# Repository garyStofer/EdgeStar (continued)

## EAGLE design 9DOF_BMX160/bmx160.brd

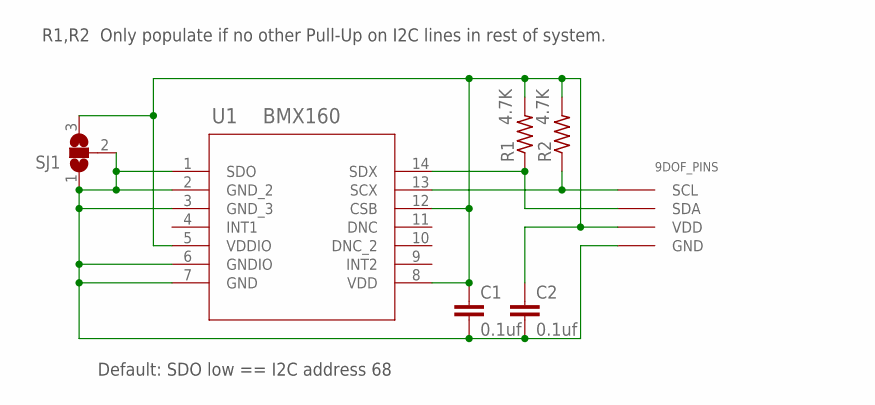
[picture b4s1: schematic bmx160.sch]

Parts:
C1, C2: 0.1uf; C0603K
MOD1: 9DOF_PINS
R1, R2: 4.7K; M0805
SJ1: SJ2W; SJ_2
U1: BMX160; BMX160_BOS-M

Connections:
GND: C1.2, C2.2, MOD1.GND, SJ1.1, SJ1.2, U1.1 (SDO), U1.2 (GND_2), U1.3 (GND_3), U1.6 (GNDIO), U1.7 (GND)
unnamed: MOD1.SDA, R1.1, U1.14 (SDX)
unnamed: MOD1.SCL, R2.1, U1.13 (SCX)
VDD: C1.1, C2.1, MOD1.VDD, R1.2, R2.2, SJ1.3, U1.5 (VDDIO), U1.8 (VDD), U1.12 (CSB)

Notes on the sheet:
Default: SDO low == I2C address 68
R1,R2 Only populate if no other Pull-Up on I2C lines in rest of system.

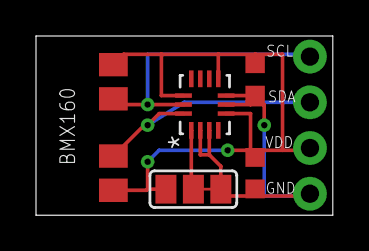
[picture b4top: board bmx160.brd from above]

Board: 2 copper layers, 16.5 x 10.0 mm, 7 parts (0 on the bottom side), 4 nets.

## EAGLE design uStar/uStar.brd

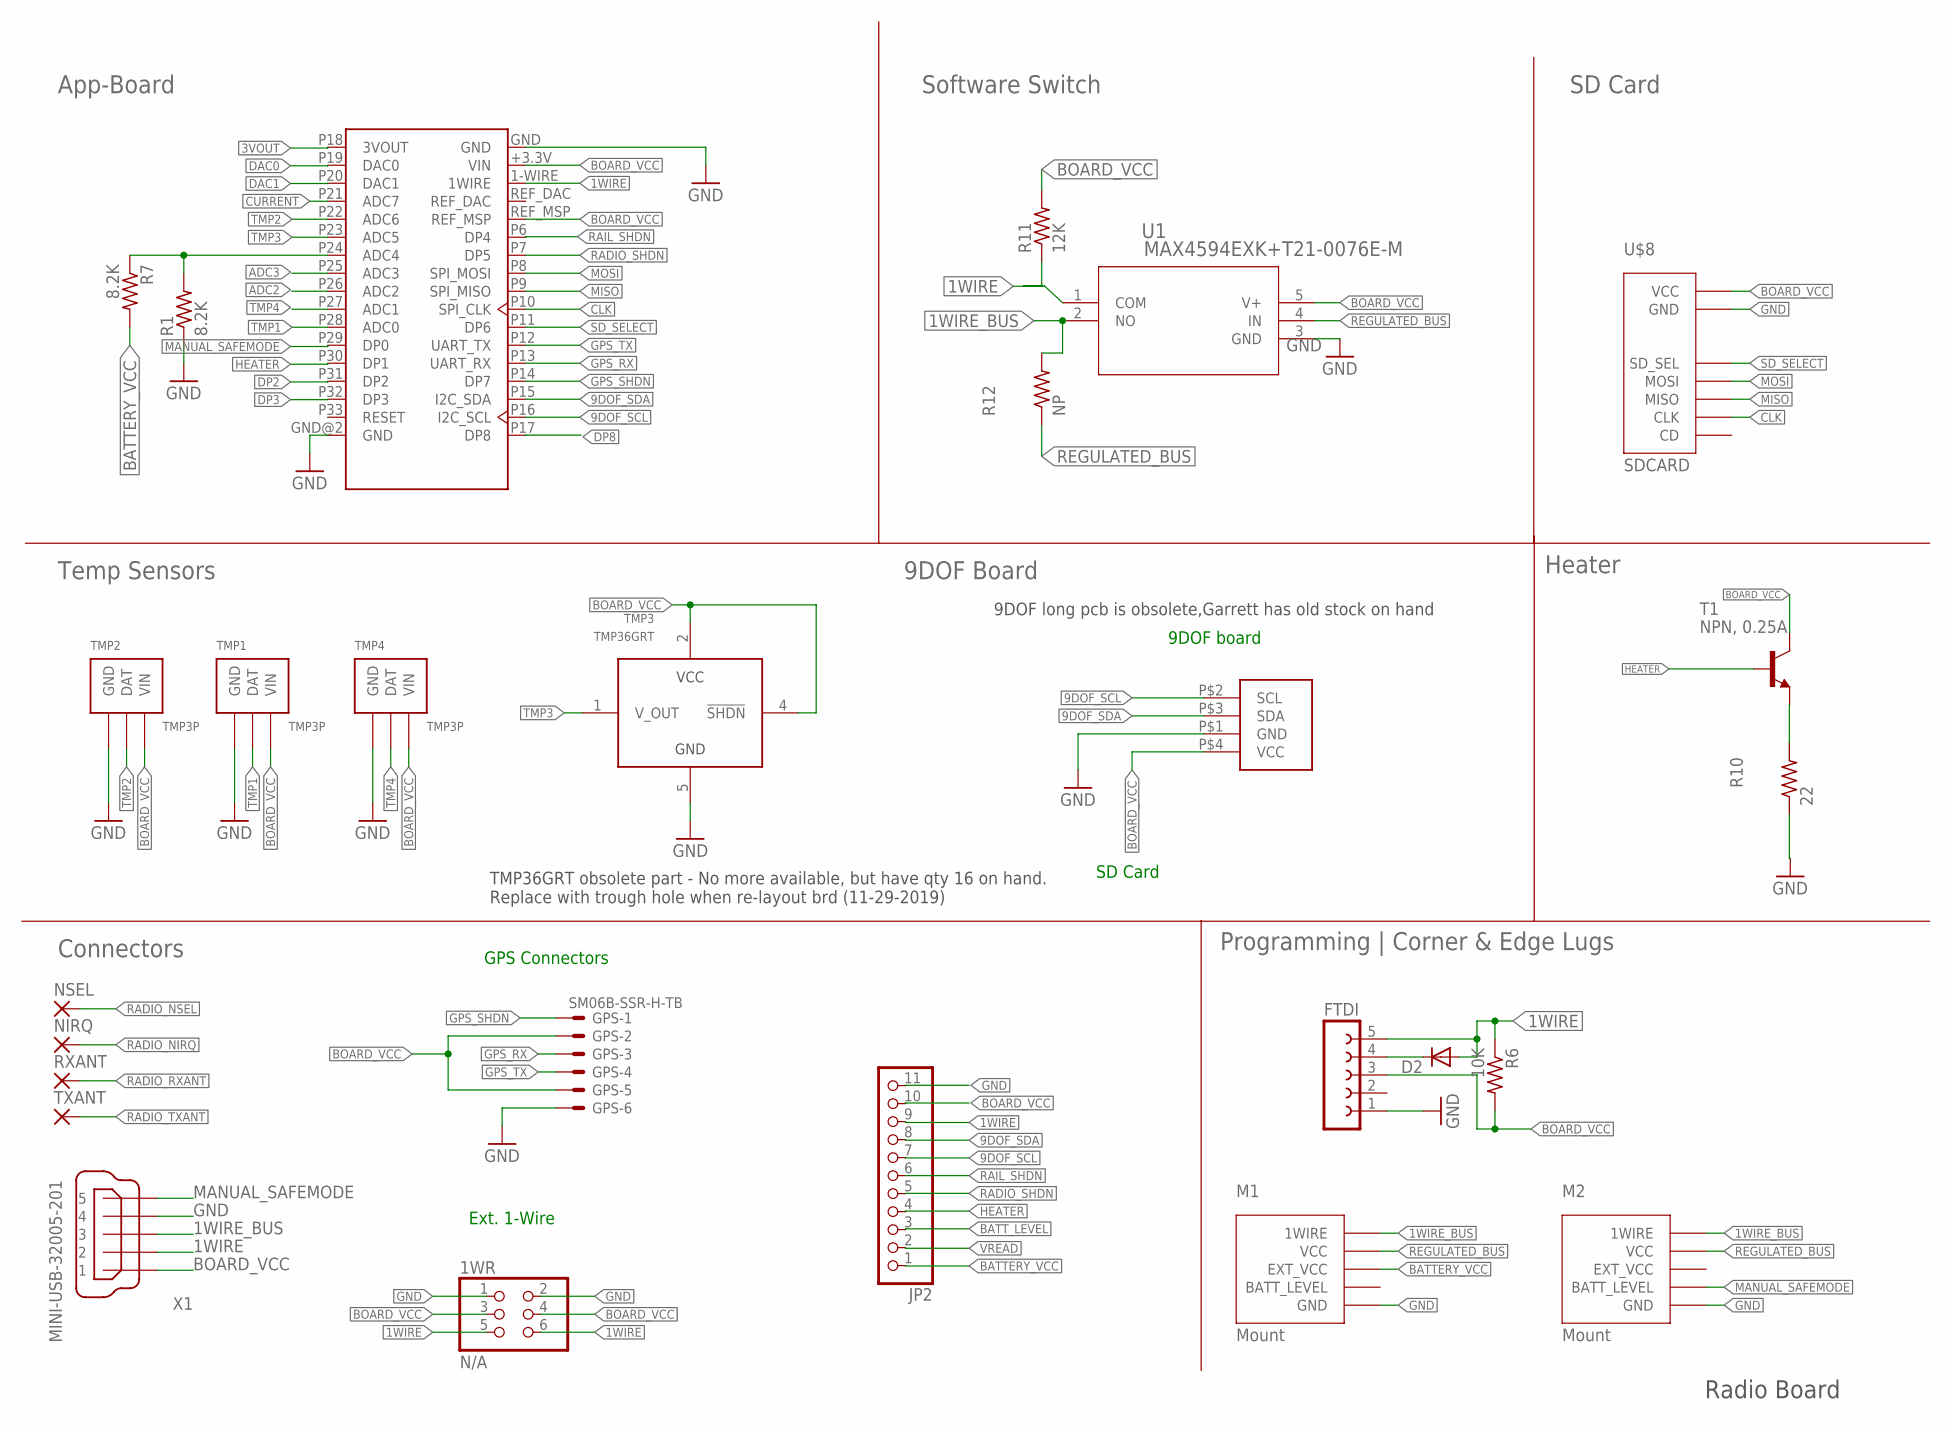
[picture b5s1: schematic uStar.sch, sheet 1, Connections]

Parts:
1WR: N/A; 2X03
D2: D-B260A; SMA-DO214AC
FTDI: FE05-1
GPS: SM06B-SSR-H-TB
JP2: PINHD-1X11; 1X11
M1, M2: Mount; 4X8MOUNT
NIRQ: 1,6/0,9
NSEL: 1,6/0,9
PCB1: 9DOF
R1, R7: 8.2K; R0805
R6: 10K; R0603
R10: 22; 0207/7
R11: 12K; R0805
R12: NP; R0805
RXANT: 1,6/0,9
T1: NPN, 0.25A; TO92-EBC-OVAL
TMP1, TMP2, TMP4: TMP3P
TMP3: TMP36GRT; SOT-23-5; DIGIKEY obsolete
TXANT: 1,6/0,9
U1: MAX4594EXK+T21-0076E-M; 21-0076E-M; DIGIKEY MAX4594EXK+TCT-ND
U$1: App-Board 1.2/1.3; APPCORE_RECEIVER
U$8: SDCARD; DIGIKEY 1568-1345-ND
X1: MINI-USB-32005-201; 32005-201

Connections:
1WIRE: 1WR.5, 1WR.6, D2.A, FTDI.5, JP2.9, R6.1, R11.1, U1.1 (COM), U$1.1-WIRE (1WIRE), X1.2
1WIRE_BUS: M1.P$2 (1WIRE), M1.P$5 (1WIRE), M2.P$2 (1WIRE), M2.P$5 (1WIRE), R12.2, U1.2 (NO), X1.3
3VOUT: U$1.P18 (3VOUT)
9DOF_SCL: JP2.7, PCB1.P$2 (SCL), U$1.P16 (I2C_SCL)
9DOF_SDA: JP2.8, PCB1.P$3 (SDA), U$1.P15 (I2C_SDA)
ADC2: U$1.P26 (ADC2)
ADC3: U$1.P25 (ADC3)
BATTERY_VCC: JP2.1, M1.P$3 (EXT_VCC), R7.2; also elsewhere on the board
BATT_LEVEL: JP2.3
BOARD_VCC: 1WR.3, 1WR.4, FTDI.3, GPS.2, GPS.5, JP2.10, PCB1.P$4 (VCC), R6.2, R11.2, T1.C, TMP1.P$3 (VIN), TMP2.P$3 (VIN), TMP3.2 (VCC), TMP3.4 (!SHDN), TMP4.P$3 (VIN), U1.5 (V+), U$1.+3.3V (VIN), U$1.REF_MSP, U$8.P$3 (VCC), X1.1; also elsewhere on the board
CLK: U$1.P10 (SPI_CLK), U$8.P$4 (CLK); also elsewhere on the board
CURRENT: U$1.P21 (ADC7); also elsewhere on the board
DAC0: U$1.P19 (DAC0)
DAC1: U$1.P20 (DAC1)
DP2: U$1.P31 (DP2)
DP3: U$1.P32 (DP3)
DP8: U$1.P17 (DP8)
GND: 1WR.1, 1WR.2, FTDI.1, GPS.6, JP2.11, M1.P$1 (GND), M1.P$8 (GND), M2.P$1 (GND), M2.P$8 (GND), PCB1.P$1 (GND), R1.1, R10.1, TMP1.P$1 (GND), TMP2.P$1 (GND), TMP3.5 (GND), TMP4.P$1 (GND), U1.3 (GND), U$1.GND, U$1.GND@2 (GND), U$8.P$5 (GND), X1.4; also elsewhere on the board
GPS_RX: GPS.3, U$1.P13 (UART_RX)
GPS_SHDN: GPS.1, U$1.P14 (DP7)
GPS_TX: GPS.4, U$1.P12 (UART_TX)
HEATER: JP2.4, T1.B, U$1.P30 (DP1)
MANUAL_SAFEMODE: M2.P$6 (BATT_LEVEL), U$1.P29 (DP0), X1.5
MISO: U$1.P9 (SPI_MISO), U$8.P$6 (MISO); also elsewhere on the board
MOSI: U$1.P8 (SPI_MOSI), U$8.P$2 (MOSI); also elsewhere on the board
unnamed: R1.2, R7.1, U$1.P24 (ADC4)
unnamed: R10.2, T1.E
unnamed: D2.K (C), FTDI.4
RADIO_NIRQ: NIRQ.1; also elsewhere on the board
RADIO_NSEL: NSEL.1; also elsewhere on the board
RADIO_RXANT: RXANT.1; also elsewhere on the board
RADIO_SHDN: JP2.5, U$1.P7 (DP5); also elsewhere on the board
RADIO_TXANT: TXANT.1; also elsewhere on the board
RAIL_SHDN: JP2.6, U$1.P6 (DP4); also elsewhere on the board
REGULATED_BUS: M1.P$4 (VCC), M1.P$7 (VCC), M2.P$4 (VCC), M2.P$7 (VCC), R12.1, U1.4 (IN); also elsewhere on the board
SD_SELECT: U$1.P11 (DP6), U$8.P$1 (SD_SEL)
TMP1: TMP1.P$2 (DAT), U$1.P28 (ADC0)
TMP2: TMP2.P$2 (DAT), U$1.P22 (ADC6)
TMP3: TMP3.1 (V_OUT), U$1.P23 (ADC5)
TMP4: TMP4.P$2 (DAT), U$1.P27 (ADC1)
VREAD: JP2.2

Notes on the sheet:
Ext. 1-Wire
App-Board
Temp Sensors
9DOF board
GPS Connectors
SD Card
Software Switch
Connectors
Programming | Corner & Edge Lugs
9DOF Board
Heater
TMP36GRT obsolete part - No more available, but have qty 16 on hand. Replace with trough hole when re-layout brd (11-29-2019)
9DOF long pcb is obsolete,Garrett has old stock on hand
Radio Board

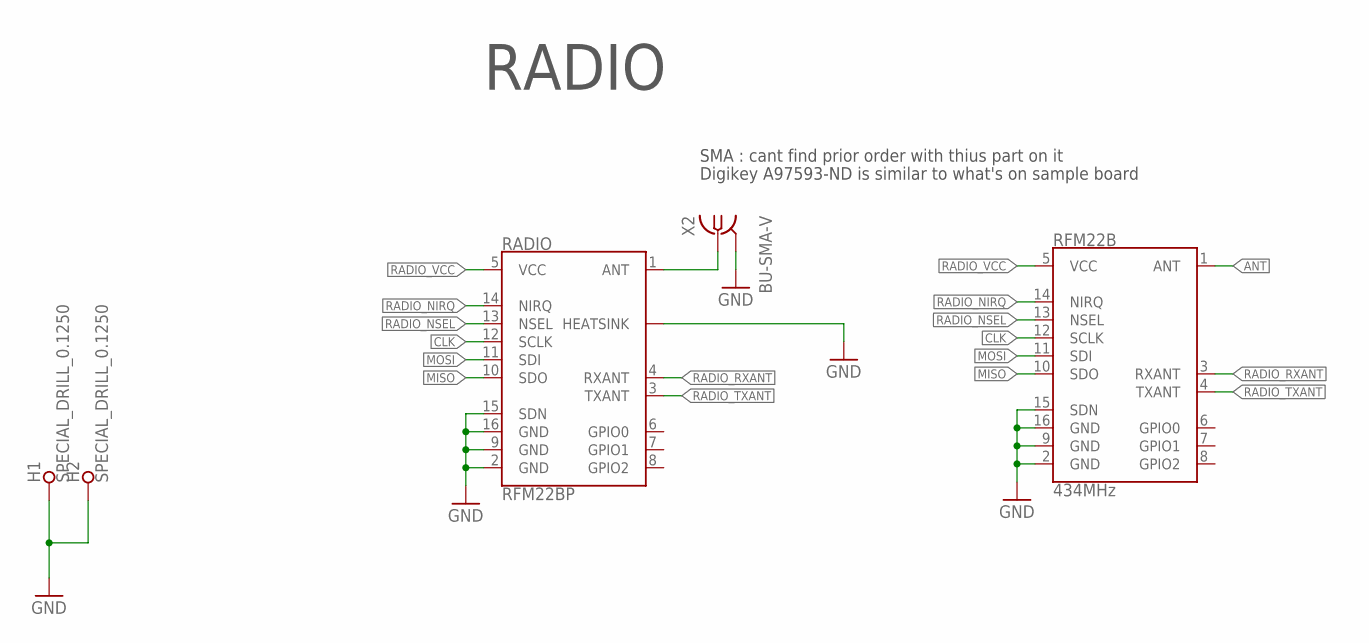
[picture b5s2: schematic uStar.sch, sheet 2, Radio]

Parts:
H1, H2: SPECIAL_DRILL_0.1250; PAD_0.1250
RADIO: RFM22BP
RFM22B: 434MHz; RFM22-XXX-S2
X2: BU-SMA-V; DIGIKEY A97593-ND

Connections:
ANT: RADIO.1 (ANT), RFM22B.1 (ANT), X2.1
CLK: RADIO.12 (SCLK), RFM22B.12 (SCLK); also elsewhere on the board
GND: H1.1, H2.1, RADIO.2 (GND), RADIO.9 (GND), RADIO.15 (SDN), RADIO.16 (GND), RADIO.P$1 (HEATSINK), RFM22B.2 (GND), RFM22B.9 (GND), RFM22B.15 (SDN), RFM22B.16 (GND), X2.2, X2.3 (2), X2.4 (2), X2.5 (2); also elsewhere on the board
MISO: RADIO.10 (SDO), RFM22B.10 (SDO); also elsewhere on the board
MOSI: RADIO.11 (SDI), RFM22B.11 (SDI); also elsewhere on the board
RADIO_NIRQ: RADIO.14 (NIRQ), RFM22B.14 (NIRQ); also elsewhere on the board
RADIO_NSEL: RADIO.13 (NSEL), RFM22B.13 (NSEL); also elsewhere on the board
RADIO_RXANT: RADIO.4 (RXANT), RFM22B.3 (RXANT); also elsewhere on the board
RADIO_TXANT: RADIO.3 (TXANT), RFM22B.4 (TXANT); also elsewhere on the board
RADIO_VCC: RADIO.5 (VCC), RFM22B.5 (VCC); also elsewhere on the board

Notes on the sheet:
RADIO
Digikey A97593-ND is similar to what's on sample board
SMA : cant find prior order with thius part on it

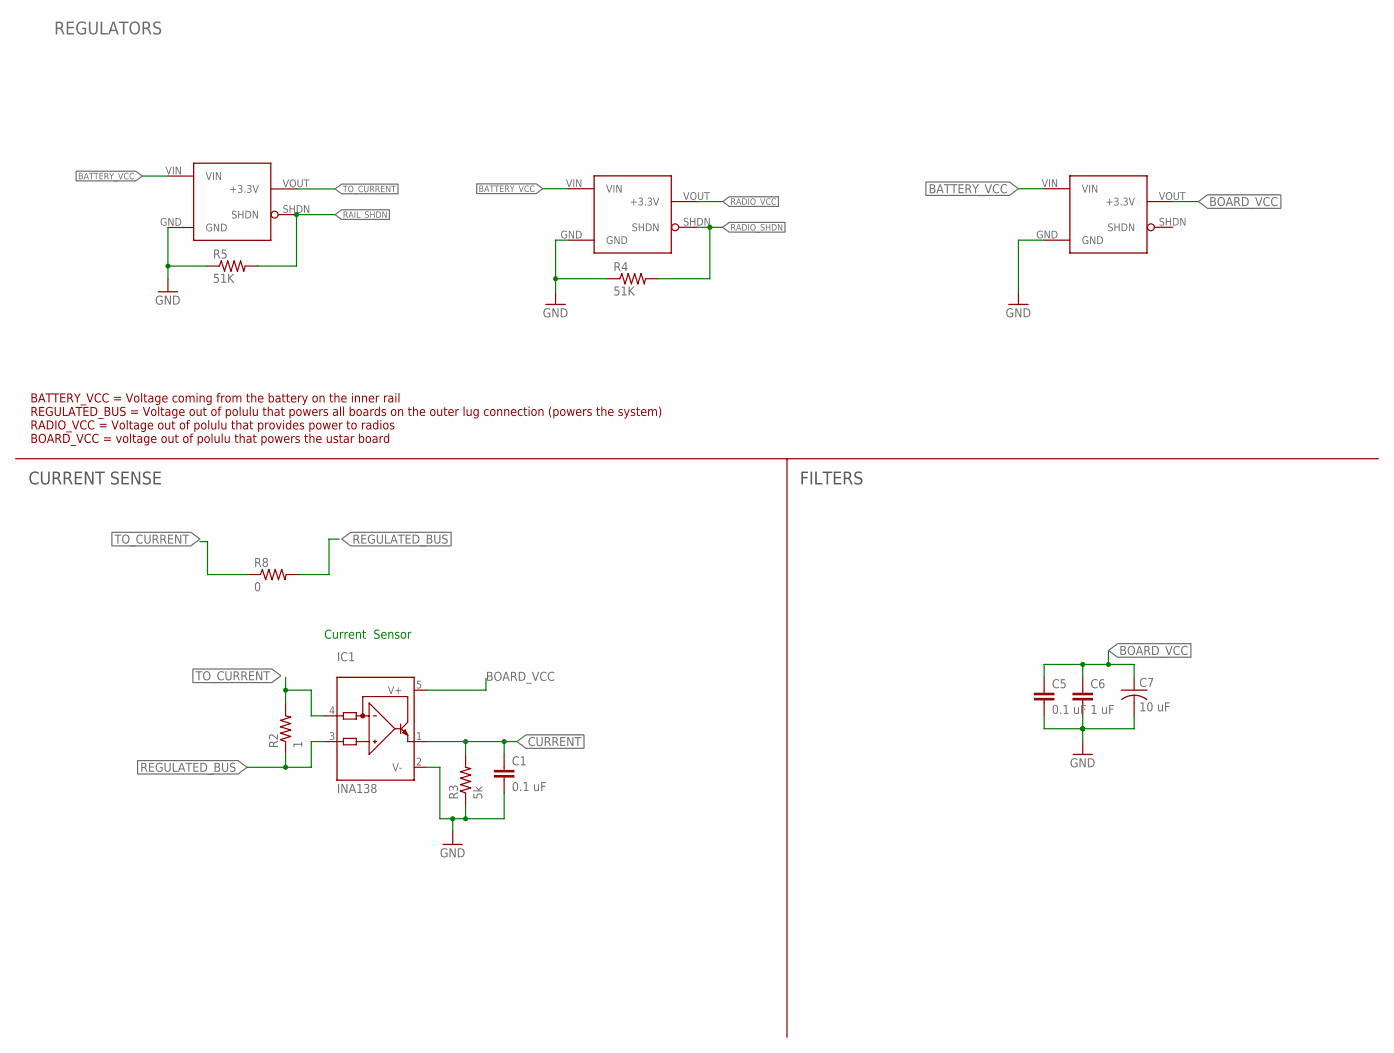
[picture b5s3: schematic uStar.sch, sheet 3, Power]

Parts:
C1, C5: 0.1 uF; C0603
C6: 1 uF; C0603
C7: 10 uF; C0805_POL
IC1: INA138; SOT23-5; MOUSER 595-INA138NA3K
R2: 1; R0603; DIGIKEY 311-1.00HRCT-ND
R3: 5k; R0603; DIGIKEY 2019-RK73B1JTTD512JCT-ND
R4, R5: 51K; R0603
R8: 0; R1210W; DIGIKEY YAG3375CT-ND
VR1, VR2, VR3: S7V8F3_VOLT_REG-3V3_1AHORZ-DOWN; S7V_DOWN; DIGIKEY 2183-2122-ND

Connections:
BATTERY_VCC: VR1.VIN, VR2.VIN, VR3.VIN; also elsewhere on the board
BOARD_VCC: C5.1, C6.1, C7.2 (1), IC1.5 (V+), VR3.VOUT (+3.3V); also elsewhere on the board
CURRENT: C1.1, IC1.1 (OUT), R3.2; also elsewhere on the board
GND: C1.2, C5.2, C6.2, C7.1 (2), IC1.2 (V-), R3.1, R4.1, R5.1, VR1.GND, VR2.GND, VR3.GND; also elsewhere on the board
RADIO_SHDN: R4.2, VR2.SHDN; also elsewhere on the board
RADIO_VCC: VR2.VOUT (+3.3V); also elsewhere on the board
RAIL_SHDN: R5.2, VR1.SHDN; also elsewhere on the board
REGULATED_BUS: IC1.3 (IN+), R2.1, R8.2; also elsewhere on the board
TO_CURRENT: IC1.4 (IN-), R2.2, R8.1, VR1.VOUT (+3.3V)

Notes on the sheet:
Current Sensor
REGULATORS
CURRENT SENSE
FILTERS
BATTERY_VCC = Voltage coming from the battery on the inner rail REGULATED_BUS = Voltage out of polulu that powers all boards on the outer lug connection (powers the system) RADIO_VCC = Voltage out of polulu that provides power to radios BOARD_VCC = voltage out of polulu that powers the ustar board

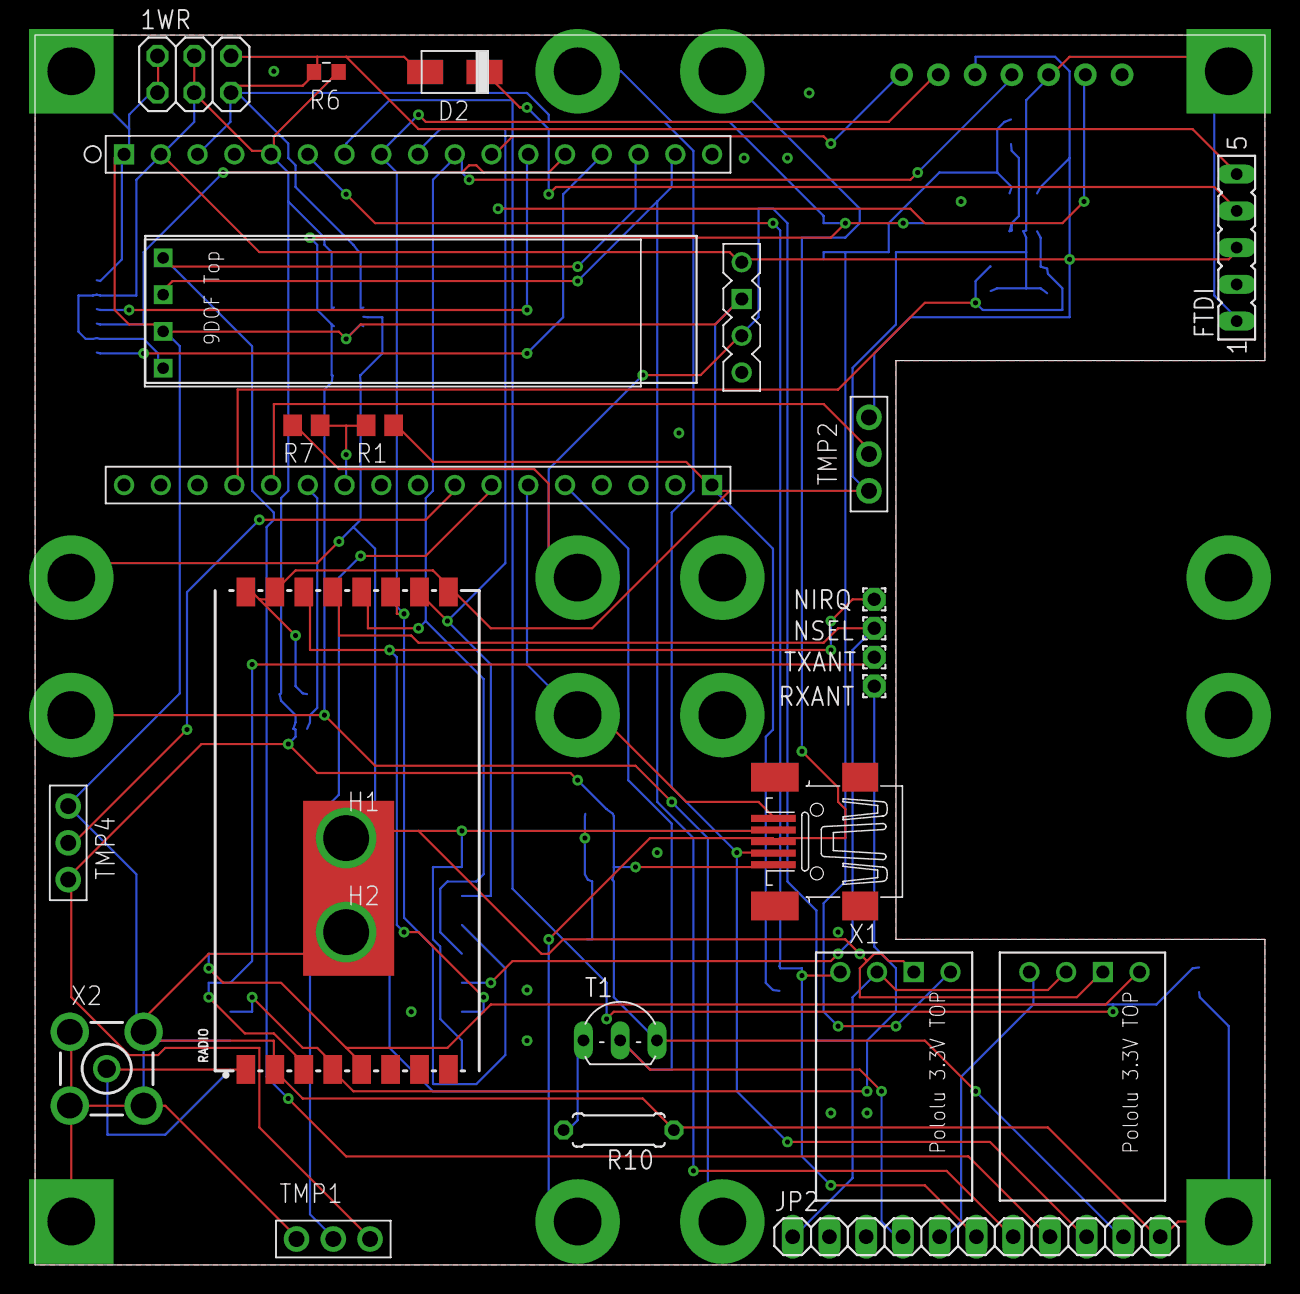
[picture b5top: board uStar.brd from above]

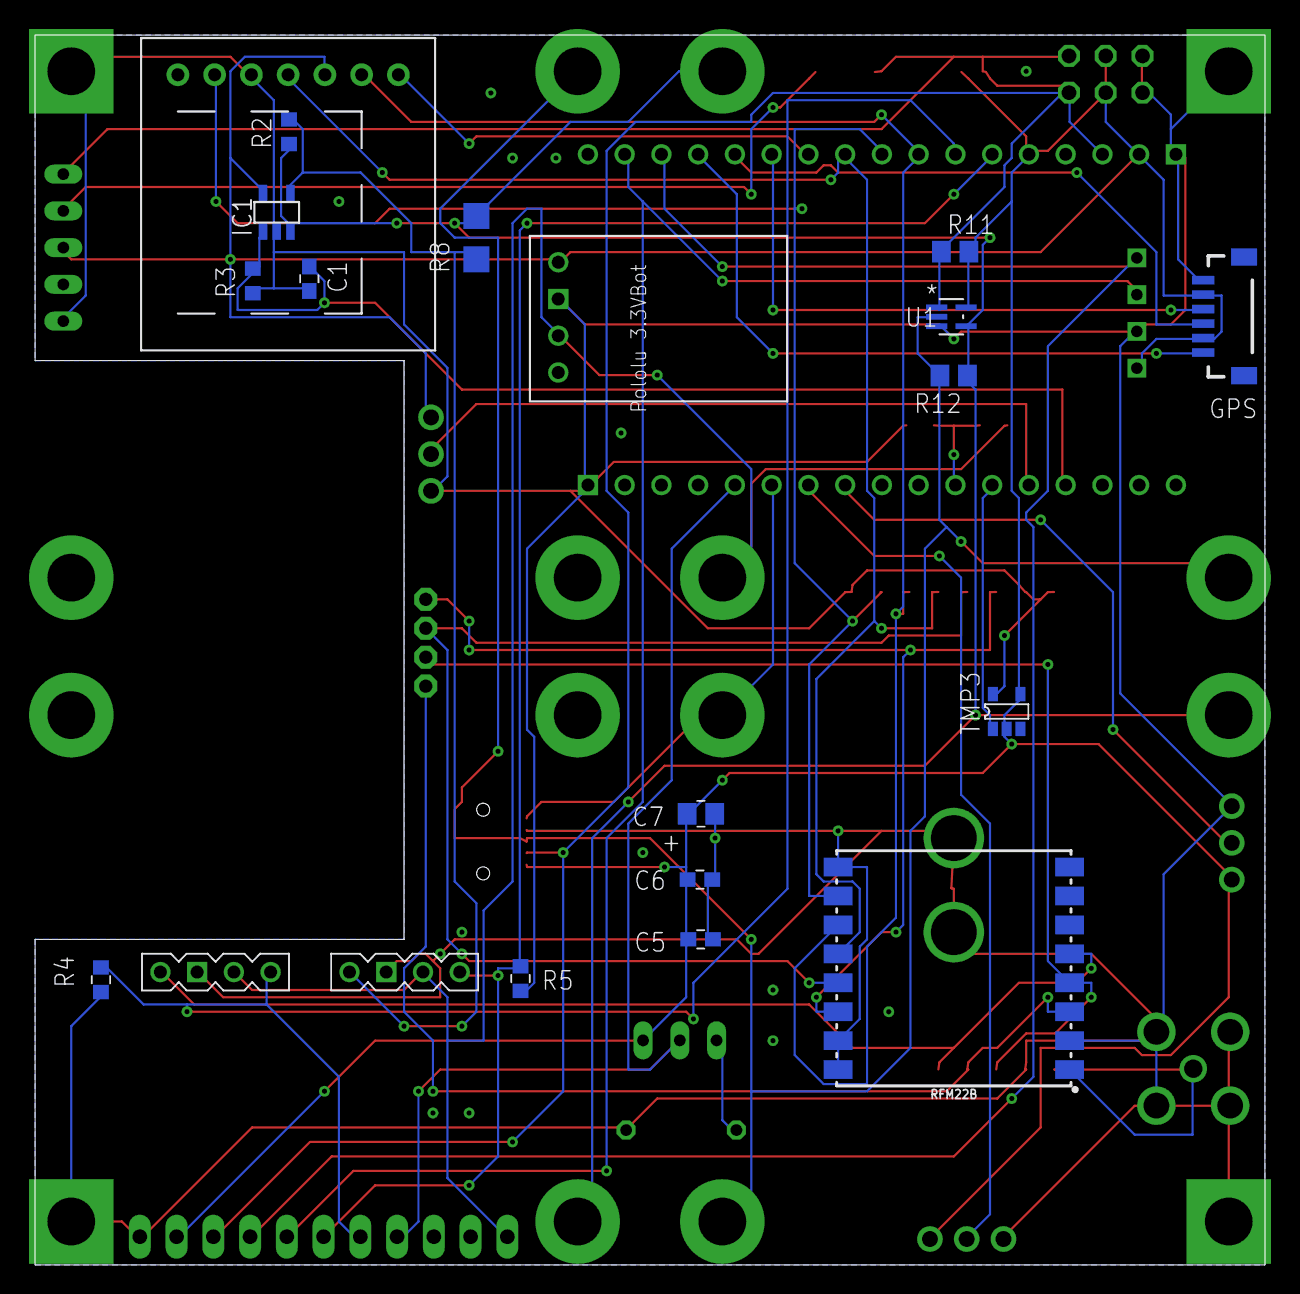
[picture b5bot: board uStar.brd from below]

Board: 2 copper layers, 85.0 x 85.0 mm, 45 parts (18 on the bottom side), 34 nets.

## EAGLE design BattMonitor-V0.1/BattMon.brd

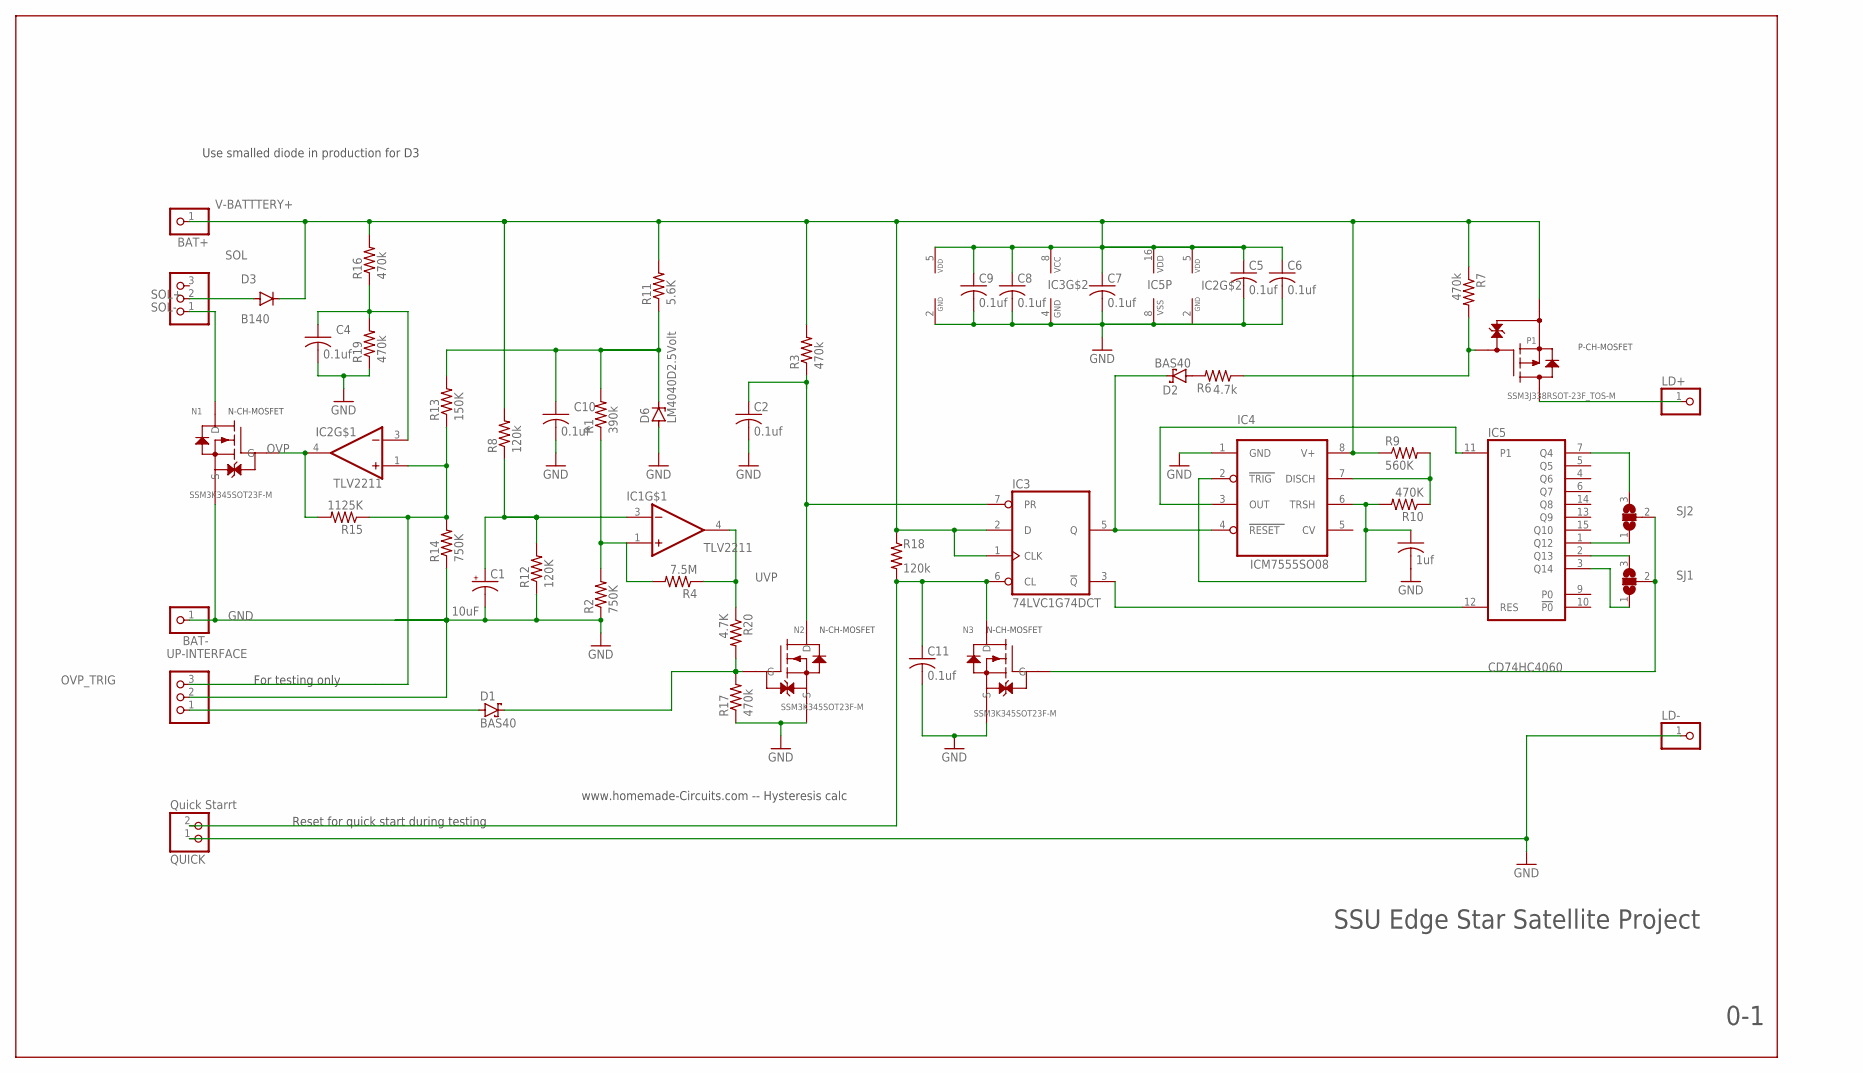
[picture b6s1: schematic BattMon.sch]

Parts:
BAT+: PINHD-1X1; 1X01
BAT-: PINHD-1X1; 1X01
C1: 10uF; E2,5-6E; DIGIKEY 399-6648-1-ND
C2, C4, C5, C6, C7, C8, C9, C10, C11: 0.1uf; C0805
C3: 1uf; C0805; DIGIKEY 311-3497-1-ND
D1, D2: BAS40; SOT23
D3: B140; SMA; DIGIKEY B260A-FDICT-ND
D6: LM4040D2.5Volt; SOT23
IC1: TLV2211; SOT23-5
IC2: TLV2211; SOT23-5; DIGIKEY 296-10500-1-ND
IC3: 74LVC1G74DCT; DCT_R-PDSO-G8; DIGIKEY SN74LVC1G74DCTR
IC4: ICM7555SO08; SO08
IC5: CD74HC4060; SO16; DIGIKEY 296-25999-1-ND
LD+: PINHD-1X1; 1X01
LD-: PINHD-1X1; 1X01
N1, N2, N3: SSM3K345SOT23F-M; SOT-23F_TOS-M
P1: SSM3J338RSOT-23F_TOS-M; SOT-23F_TOS-M
QUICK: Quick Starrt; 1X02
R1: 390k; R0805
R2, R14: 750K; R0805
R3, R7, R16, R17, R19: 470k; R0805
R4: 7.5M; R0805
R6: 4.7k; R0805
R8, R18: 120k; R0805
R9: 560K; R0805
R10: 470K; R0805
R11: 5.6K; R0805
R12: 120K; R0805
R13: 150K; R0805
R15: 1125K; R0805
R20: 4.7K; R0805
SJ1, SJ2: SJ2W; SJ_2
SOL: PINHD-1X3; 1X03
UP-INTERFACE: PINHD-1X3; 1X03

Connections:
GND: BAT-.1, C1.-, C2.2, C3.2, C4.2, C5.2, C6.2, C7.2, C8.2, C9.2, C10.2, C11.2, D6.2 (A), IC1.2 (VDD_GND), IC2.2 (VDD_GND), IC3.4 (GND), IC4.1 (GND), IC5.8 (VSS), LD-.1, N1.2 (S), N2.2 (S), N3.2 (S), QUICK.1, R2.1, R12.1, R14.1, R17.1, R19.1, UP-INTERFACE.2
unnamed: IC1.1 (+IN), R1.1, R2.2, R4.2
unnamed: D2.3 (C), IC3.5 (Q), IC4.4 (RESET)
unnamed: IC3.3 (!Q), IC5.12 (RES)
unnamed: D1.3 (C), N2.1 (G), R17.2, R20.2
unnamed: C1.+, IC1.3 (-IN), R8.1, R12.2
unnamed: D2.1 (A), R6.2
unnamed: C10.1, D6.1 (C), R1.2, R11.1, R13.2
unnamed: D1.1 (A), UP-INTERFACE.1
unnamed: C3.1, IC4.2 (TRIG), IC4.6 (TRSH), R10.2
unnamed: N3.1 (G), SJ1.2, SJ2.2
unnamed: IC4.7 (DISCH), R9.2, R10.1
unnamed: IC4.3 (OUT), IC5.11 (P1)
unnamed: P1.1, R6.1, R7.2
unnamed: IC5.3 (Q14), SJ1.1
unnamed: IC5.2 (Q13), SJ1.3
unnamed: IC5.1 (Q12), SJ2.1
unnamed: IC5.7 (Q4), SJ2.3
unnamed: LD+.1, P1.3
unnamed: C11.1, IC3.6 (CL), N3.3 (D), QUICK.2, R18.2
unnamed: C4.1, IC2.3 (-IN), R16.1, R19.2
OVP: IC2.4 (OUT), N1.1 (G), R15.2
OVP_TRIG: IC2.1 (+IN), R13.1, R14.2, R15.1, UP-INTERFACE.3
SOL+: D3.A, SOL.2
SOL-: N1.3 (D), SOL.1
UVP: IC1.4 (OUT), R4.1, R20.1
UVP_: C2.1, IC3.7 (PR), N2.3 (D), R3.1
V-BATTTERY+: BAT+.1, C5.1, C6.1, C7.1, C8.1, C9.1, D3.C, IC1.5 (VDD), IC2.5 (VDD), IC3.1 (CLK), IC3.2 (D), IC3.8 (VCC), IC4.8 (V+), IC5.16 (VDD), P1.2, R3.2, R7.1, R8.2, R9.1, R11.2, R16.2, R18.1

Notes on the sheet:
SSU Edge Star Satellite Project
0-1
For testing only
P-CH-MOSFET
N-CH-MOSFET
Use smalled diode in production for D3
Reset for quick start during testing
www.homemade-Circuits.com -- Hysteresis calc

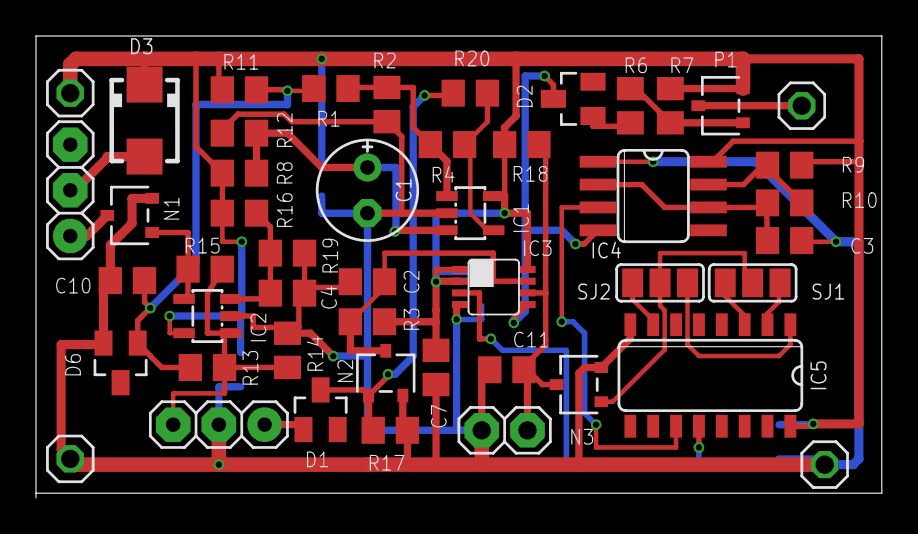
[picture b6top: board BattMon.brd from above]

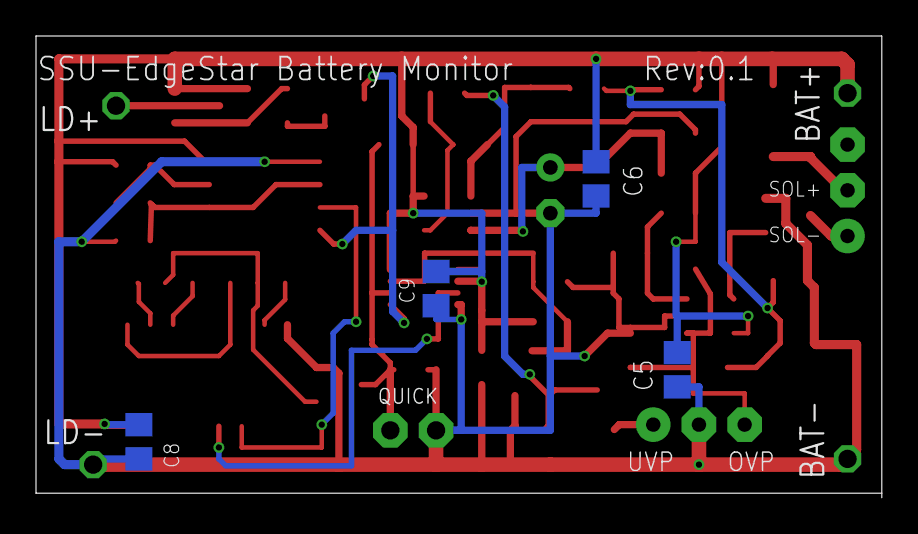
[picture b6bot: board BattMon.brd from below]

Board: 2 copper layers, 47.0 x 25.7 mm, 52 parts (4 on the bottom side), 28 nets.

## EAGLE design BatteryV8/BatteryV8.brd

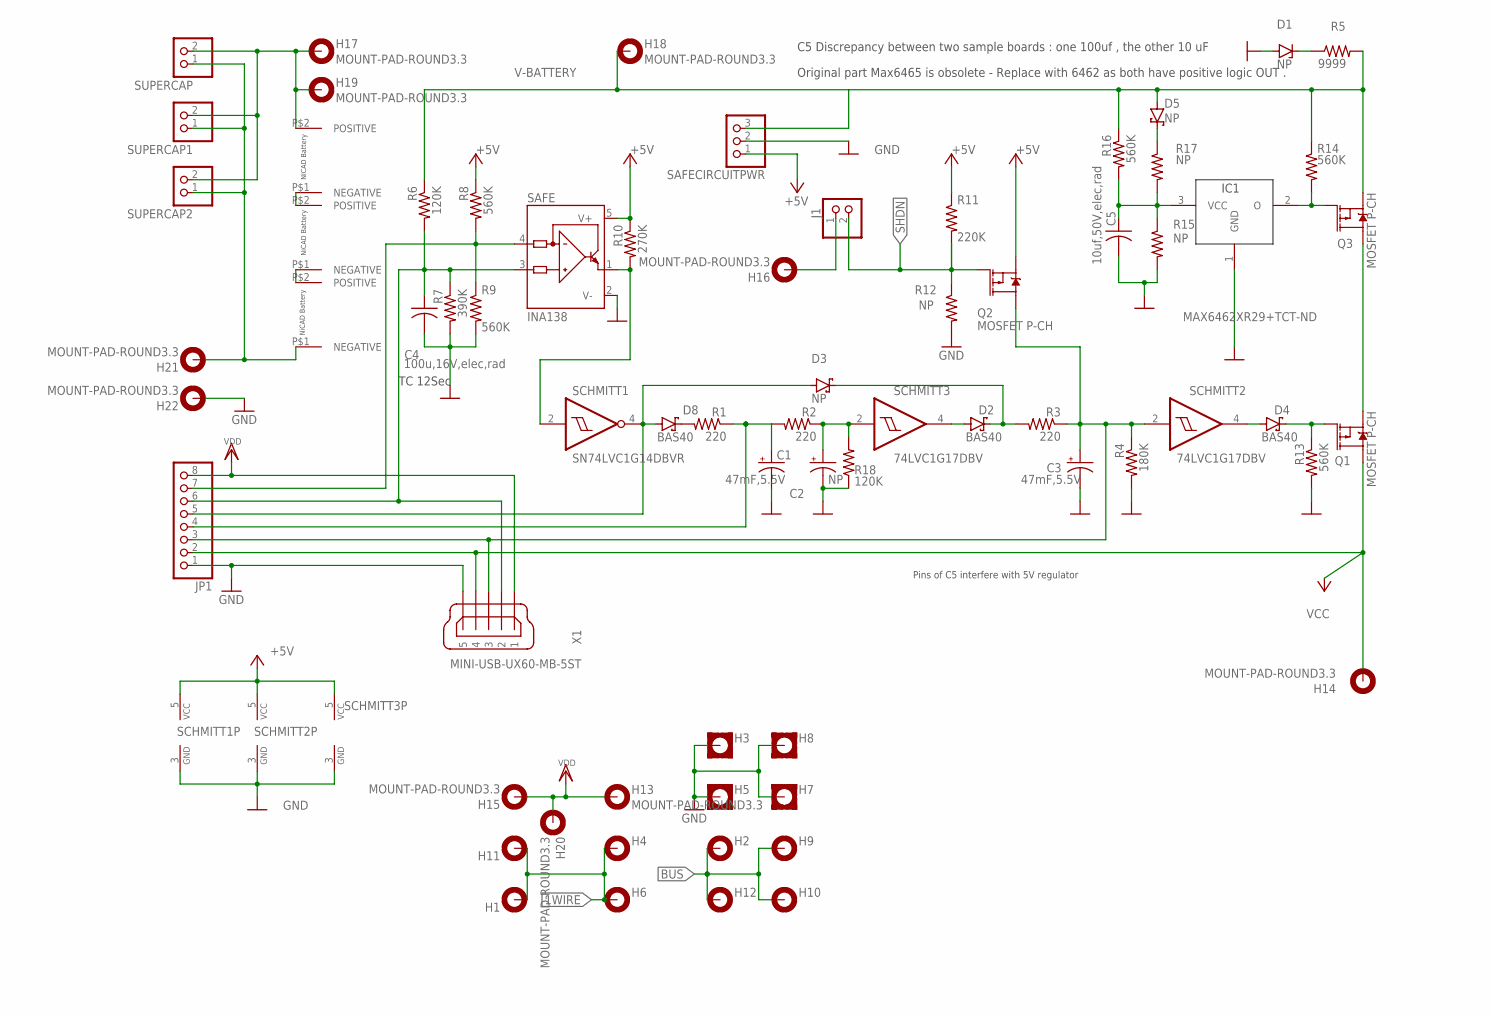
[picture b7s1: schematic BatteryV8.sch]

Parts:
C1, C3: 47mF,5.5V; 153CLV-1010; DIGIKEY 399-16033-1-ND
C2: NP; 153CLV-1010
C4: 100u,16V,elec,rad; C050-030X075; DIGIKEY 399-6648-1-ND
C5: 10uf,50V,elec,rad; C050-030X075; DIGIKEDY P807-ND
D1: NP; DO35Z10
D2, D4, D8: BAS40; SOT23; DIGIKEY BAS40-04fdict-ND
D3: NP; SOT23; DIGIKEY BAS40-04fdict-ND
D5: NP; SOT23
H1, H2, H4, H6, H9, H10, H11, H12, H13, H14, H15, H16, H17, H18, H19, H20, H21, H22: MOUNT-PAD-ROUND3.3; 3,3-PAD
H3, H5, H7, H8: MOUNT-PAD-SQUARE3.3; 3,3-PAD-SQUARE
IC1: MAX6462XR29T; EDGECUBE_SC70-3; DIGIKEY MAX6462XR29+TCT-ND
J1: PINHD-1X2; 1X02
JP1: PINHD-1X8; 1X08
Q1, Q2, Q3: MOSFET P-CH; SOT23-3; DIGIKEY SSM3J338RLFCT-ND
R1, R2, R3: 220; R0805
R4: 180K; R0805
R5: 9999; 0207/10
R6, R18: 120K; R0805
R7: 390K; R0805
R8, R9, R13, R14, R16: 560K; R0805
R10: 270K; R0805
R11: 220K; R0805
R12, R15, R17: NP; R0805
SAFE: INA138; SOT23-5; MOUSER 595-INA138NA3K
SAFECIRCUITPWR: PINHD-1X3; 1X03
SCHMITT1: SN74LVC1G14DBVR; SOT23-5; DIGIKET 296-11607-1-ND
SCHMITT2, SCHMITT3: 74LVC1G17DBV; SOT23-5; DIGIKEY 296-11933-1-ND
SUPERCAP, SUPERCAP1, SUPERCAP2: PINHD-1X2; 1X02
U$5, U$6, U$7: JST-WATCH_AA-BATT
X1: MINI-USB-UX60-MB-5ST; UX60-MB-5ST

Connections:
1WIRE: H1.B3,3, H4.B3,3, H6.B3,3, H11.B3,3
+5V: Q2.2 (S), R8.1, R10.1, R11.1, SAFE.5 (V+), SAFECIRCUITPWR.1, SCHMITT1.5 (VCC), SCHMITT2.5 (VCC), SCHMITT3.5 (VCC)
BUS: H2.B3,3, H9.B3,3, H10.B3,3, H12.B3,3
GND: C1.-, C2.-, C3.-, C4.2, C5.2, D1.A, H3.B3,3, H5.B3,3, H7.B3,3, H8.B3,3, H22.B3,3, IC1.1 (GND), JP1.1, R4.2, R7.2, R9.2, R12.2, R13.2, R15.2, R18.1, SAFE.2 (V-), SAFECIRCUITPWR.2, SCHMITT1.3 (GND), SCHMITT2.3 (GND), SCHMITT3.3 (GND), X1.5
unnamed: C3.+, JP1.3, Q2.3 (D), R3.1, R4.1, SCHMITT2.2 (I), X1.3
unnamed: D8.3 (C), R1.2
unnamed: C1.+, JP1.4, R1.1, R2.2
unnamed: D4.1 (A), SCHMITT2.4 (O)
unnamed: D5.3 (C), R17.1
unnamed: C2.+, R2.1, R18.2, SCHMITT3.2 (I)
unnamed: C4.1, JP1.6, R6.2, R7.1, SAFE.3 (IN+), X1.2
unnamed: H21.B3,3, SUPERCAP.1, SUPERCAP1.1, SUPERCAP2.1, U$5.P$1 (NEGATIVE)
unnamed: D1.C, R5.1
unnamed: D2.1 (A), SCHMITT3.4 (O)
unnamed: R10.2, SAFE.1 (OUT), SCHMITT1.2 (I)
unnamed: D2.3 (C), D3.3 (C), R3.2
unnamed: JP1.7, R8.2, R9.1, SAFE.4 (IN-)
unnamed: D4.3 (C), Q1.1 (G), R13.1
unnamed: IC1.2 (O), Q3.1 (G), R14.2
unnamed: C5.1, IC1.3 (VCC), R15.1, R16.2, R17.2
unnamed: U$5.P$2 (POSITIVE), U$6.P$1 (NEGATIVE)
unnamed: H17.B3,3, H19.B3,3, SUPERCAP.2, SUPERCAP1.2, SUPERCAP2.2, U$7.P$2 (POSITIVE)
unnamed: Q1.2 (S), Q3.3 (D)
unnamed: U$6.P$2 (POSITIVE), U$7.P$1 (NEGATIVE)
unnamed: H16.B3,3, J1.1
unnamed: D3.1 (A), D8.1 (A), JP1.5, SCHMITT1.4 (O)
SHDN: J1.2, Q2.1 (G), R11.2, R12.1
V-BATTERY: D5.1 (A), H18.B3,3, Q3.2 (S), R5.2, R6.1, R14.1, R16.1, SAFECIRCUITPWR.3
VCC: H14.B3,3, JP1.2, Q1.3 (D), X1.4
VDD: H13.B3,3, H15.B3,3, H20.B3,3, JP1.8, X1.1

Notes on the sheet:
Pins of C5 interfere with 5V regulator
NiCAD Battery
C5 Discrepancy between two sample boards : one 100uf , the other 10 uF
Original part Max6465 is obsolete - Replace with 6462 as both have positive logic OUT .
IC1
TC 12Sec
